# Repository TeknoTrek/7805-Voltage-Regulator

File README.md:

# 7805 Voltage Regulator
 This repository contains all the files necessary to design and simulate a 7805 voltage regulator circuit. The 7805 is a popular linear voltage regulator that provides a stable 5V output from a higher input voltage (typically 7-35V). It’s commonly used in electronics projects to power microcontrollers, sensors, and other components that require a reliable 5V supply.

### Features
- **Schematic Design:** A detailed circuit schematic illustrating the 7805 voltage regulator in operation, along with essential components like input/output capacitors for smooth performance.
- **PCB Design:** A custom-designed PCB layout that allows for compact and efficient mounting of the 7805 regulator circuit.
- **3D Model:** A 3D visualization of the PCB to better understand the physical layout and design.
- **Simulation Files:** Test the voltage regulator performance through simulation files provided for accurate results.
- **KiCad Project:** The complete KiCad project, including schematic, PCB design, and Gerber files for fabrication.
### Usage:
1- Clone or download the repository.

2- Open the project in KiCad to view or modify the schematic and PCB layout.

3- Simulate the design using the provided simulation files.

4- Export Gerber files to manufacture the PCB if needed.
### Applications:
The 7805 voltage regulator circuit is widely used in various electronic projects, including:

- Power supply circuits for microcontroller-based systems.
- Regulating voltage for sensor modules and other peripherals.
- General purpose 5V DC power applications.

### Watch the Development Process
You can follow along with the entire development process of the 7805 Voltage Regulator Circuit on my[ YouTube channel](https://youtu.be/-1nnuz-Jnwk). I document each step, from initial design to final testing, providing insights and tips along the way. Don’t forget to subscribe for more electronics projects!

[[7805 Voltage Regulator]](https://youtu.be/-1nnuz-Jnwk)

## 📸 3D Model Preview

## 📸 7805 Voltage Regulator Circuit

## 📸 PCB

## License
This project is licensed under the MIT License – see the LICENSE file for details.

Feel free to adjust this based on additional files or details you include in the repository!

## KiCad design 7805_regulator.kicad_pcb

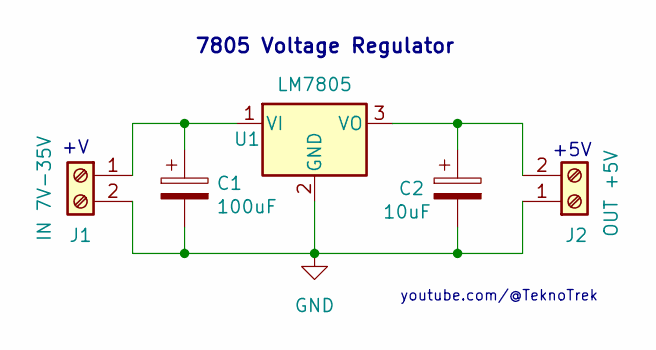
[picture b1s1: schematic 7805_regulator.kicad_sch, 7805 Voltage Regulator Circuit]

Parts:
C1: 100uF; CP_Radial_D5.0mm_P2.50mm
C2: 10uF; CP_Radial_D5.0mm_P2.50mm
J1: IN 7V-35V; TerminalBlock_bornier-2_P5.08mm
J2: OUT +5V; TerminalBlock_bornier-2_P5.08mm
U1: LM7805; TO-220-3_Vertical

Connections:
GND: C1.2, C2.2, J1.2, J2.1, U1.2 (GND)
unnamed: C1.1, J1.1, U1.1 (VI)
unnamed: C2.1, J2.2, U1.3 (VO)

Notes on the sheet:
7805 Voltage Regulator
youtube.com/@TeknoTrek
+5V

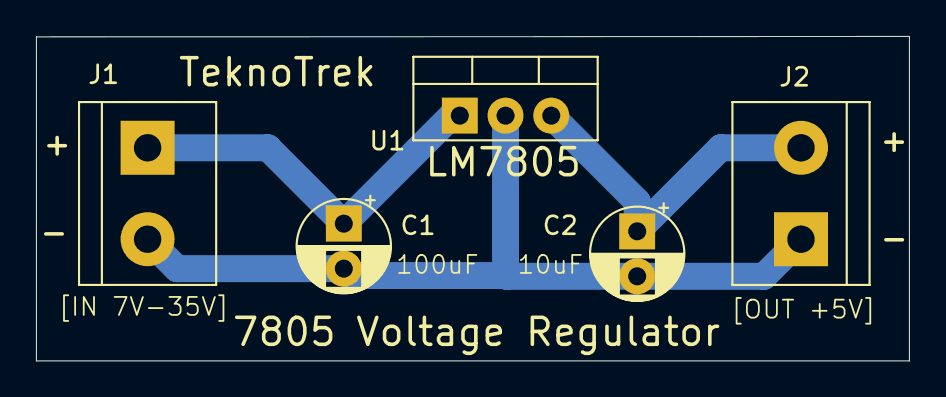
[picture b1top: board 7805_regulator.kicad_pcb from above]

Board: 2 copper layers, 48.5 x 18.0 mm, 5 parts (0 on the bottom side), 3 nets.

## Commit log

2024-09-29 Update README.md
    Update README.md
2024-09-29 Update
    Update
